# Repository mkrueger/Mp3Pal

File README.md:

# MP3Pal
MP3 player for kids based tonunio and Hörbert design.

## Features

 * Plays audio from a SD Card
 * Select playlists via 12 buttons and rfid tags

## Part list

* Arduino Nano
* DFPlayer mini
* Speaker Visaton FR 10 HM
* Guitar Potentiometer
* 74HC238, 74HC153
* 9 Arcade buttons + 3 Acracde buttons with LED
* AZDelivery Battery Expansion Shield 18650
* 18650 Battery
* Göldo Dome Chrome
* Handle from DIY Store
* Resistors 5x 10k, 1x 1k, 3x 100
* 1 Capacitor 100 uF (optional)
* RFID tags, magnets and figures
* Threads for 3D prints (I use the ones from Ruthex) M2, M3, M4
* Wires
  - JST 2.5 Connectors & Wires
  - Mini Micro JST 2.0 (with cables & pin connectors)

… to be continued (but it's below 100 Euro - if you get it from ali express it's maybe ~50)

## Schematic

## Alternatives

Tonunio

https://www.voss.earth/tonuino/

KidsMP3Player

https://github.com/ghmartin77/KidsMP3Player

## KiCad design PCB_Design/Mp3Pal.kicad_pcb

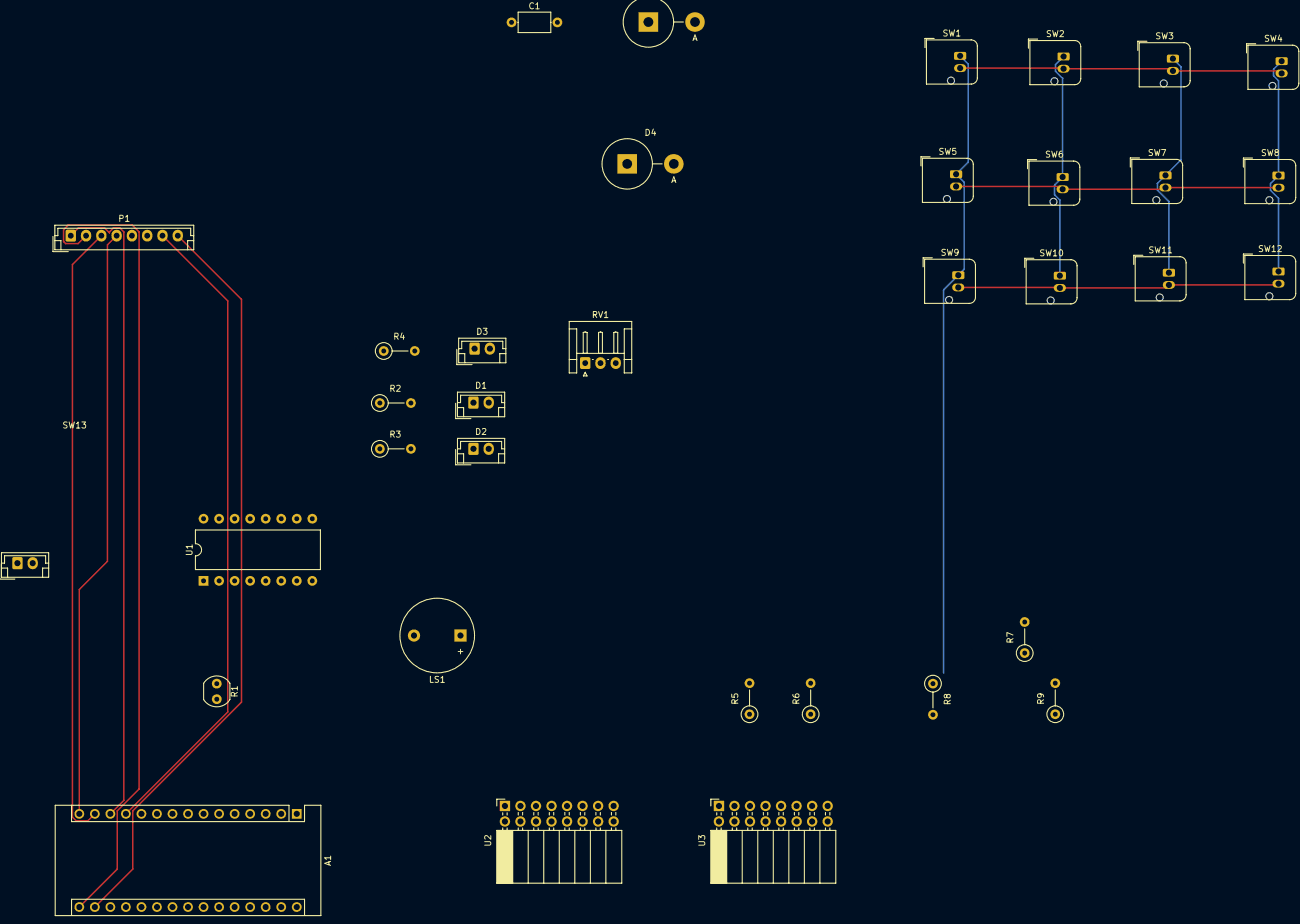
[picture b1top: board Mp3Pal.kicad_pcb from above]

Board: 2 copper layers, 35 parts (0 on the bottom side), 34 nets.

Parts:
A1: Arduino_Nano_v2.x; Arduino_Nano
C1: C; C_Axial_L5.1mm_D3.1mm_P7.50mm_Horizontal
D1, D2, D3: LED; JST_EH_B2B-EH-A_1x02_P2.50mm_Vertical
D4, D5: D; D_5KPW_P7.62mm_Vertical_AnodeUp
LS1: Speaker; Buzzer_12x9.5RM7.6
P1: RFID-RC522-MODULE; JST_EH_B8B-EH-A_1x08_P2.50mm_Vertical
R1: 1k; R_LDR_4.9x4.2mm_P2.54mm_Vertical
R2, R3, R4: 100R; R_Axial_DIN0207_L6.3mm_D2.5mm_P5.08mm_Vertical
R5, R6, R8, R9: 10k; R_Axial_DIN0207_L6.3mm_D2.5mm_P5.08mm_Vertical
R7: R; R_Axial_DIN0207_L6.3mm_D2.5mm_P5.08mm_Vertical
RV1: R_POT_US; JST_EH_S3B-EH_1x03_P2.50mm_Horizontal
SW1, SW2, SW3, SW4, SW5, SW6, SW7, SW8, SW9, SW10, SW11, SW12: SW_Push; JST_JWPF_B02B-JWPF-SK-R_1x02_P2.00mm_Vertical
SW13: SW_DIP_x01; JST_EH_B2B-EH-A_1x02_P2.50mm_Vertical
U1: DFPLAYER_MINI; DIP-16_W10.16mm
U2: 74HC238; PinSocket_2x08_P2.54mm_Horizontal
U3: 74HC153; PinSocket_2x08_P2.54mm_Horizontal

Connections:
GND: A1.4, C1.2, D1.1, D2.1, D3.1, D4.1, D5.1, D5.2, R5.2, R6.2, R7.2, R8.2, R9.2, RV1.1, U2.3, U2.4, U2.5, U2.8, U3.1, U3.8
unnamed: A1.5, U1.3
unnamed: A1.6, R1.2
unnamed: A1.7, U1.16
unnamed: A1.9, R4.2
unnamed: A1.10, R3.2
unnamed: A1.11, R2.2
unnamed: A1.12, P1.7
unnamed: A1.13, P1.1
unnamed: A1.14, P1.3
unnamed: A1.15, P1.4
unnamed: A1.16, P1.2
unnamed: A1.17, P1.8
unnamed: A1.19, U2.1
unnamed: A1.20, U2.2
unnamed: A1.21, U3.14
unnamed: A1.22, U3.2
unnamed: A1.23, R9.1, U3.7
unnamed: A1.26, RV1.2
unnamed: D1.2, R2.1
unnamed: D2.2, R3.1
unnamed: D3.2, R4.1
unnamed: D4.2, U1.7
unnamed: LS1.1, U1.8
unnamed: LS1.2, U1.6
unnamed: R1.1, U1.2
unnamed: R5.1, SW4.1, SW8.1, SW12.1, U3.6
unnamed: R6.1, SW3.1, SW7.1, SW11.1, U3.5
unnamed: R7.1, SW2.1, SW6.1, SW10.1, U3.4
unnamed: R8.1, SW1.1, SW5.1, SW9.1, U3.3
unnamed: SW1.2, SW2.2, SW3.2, SW4.2, U2.13
unnamed: SW5.2, SW6.2, SW7.2, SW8.2, U2.14
unnamed: SW9.2, SW10.2, SW11.2, SW12.2, U2.15
VCC: A1.30, C1.1, P1.6, RV1.3, SW13.2, U1.1, U2.16, U3.16

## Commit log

2021-05-30 Added source code.
2021-05-31 Worked on chassis design.
2021-07-08 Added old design, improved cad designs
2021-07-31 test.
